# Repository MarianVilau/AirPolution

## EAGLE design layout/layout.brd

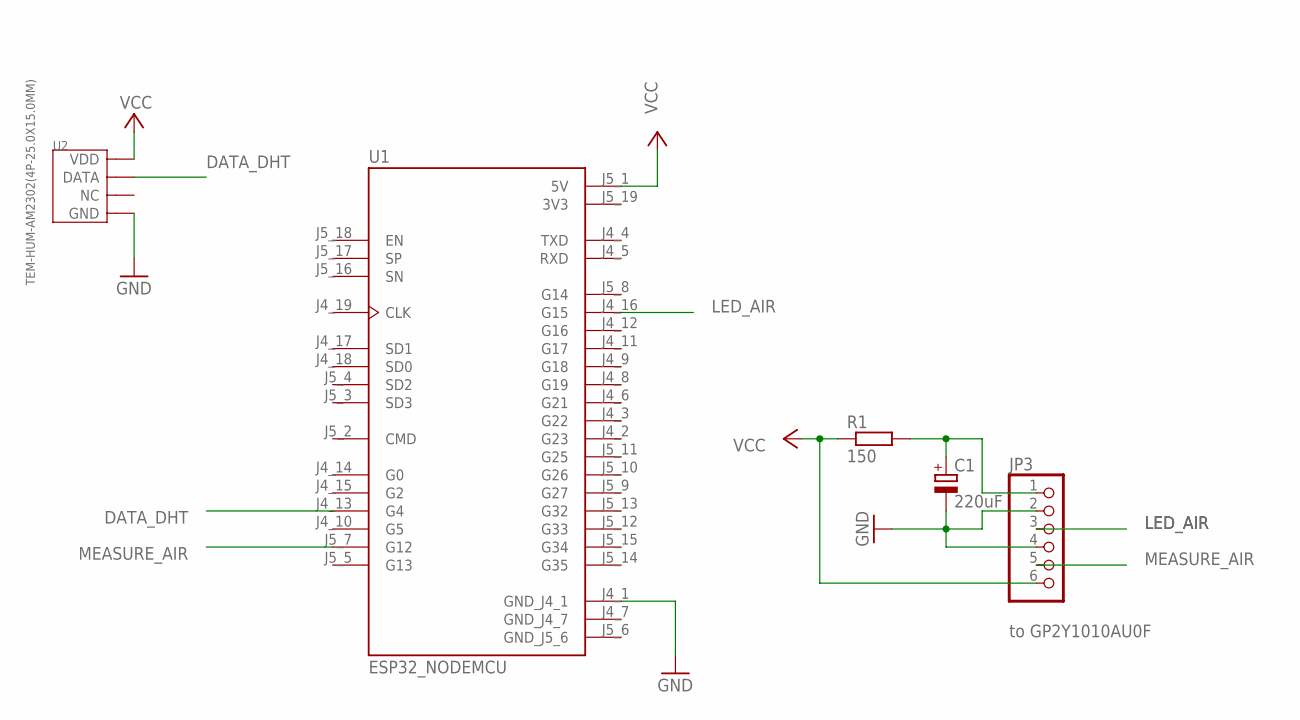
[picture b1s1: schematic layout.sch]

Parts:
C1: 220uF; E2-5
JP3: to GP2Y1010AU0F; 1X06
R1: 150; 0204/7
U1: ESP32_NODEMCU; MODULE_ESP32_NODEMCU
U2: TEM-HUM-AM2302(4P-25.0X15.0MM); SNR4-2.54-25.0X15.0X7.0MM

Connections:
3V3: U1.J5_19 (3V3)
DATA_DHT: U1.J4_13 (G4), U2.P$2 (DATA)
GND: C1.-, JP3.2, JP3.4, U1.J4_1 (GND_J4_1), U2.P$4 (GND)
GND_J4_7: U1.J4_7 (GND_J4_7)
GND_J5_6: U1.J5_6 (GND_J5_6)
LED_AIR: JP3.3, U1.J4_16 (G15)
MEASURE_AIR: JP3.5, U1.J5_7 (G12)
unnamed: C1.+, JP3.1, R1.2
VCC: JP3.6, R1.1, U1.J5_1 (5V), U2.P$1 (VDD)

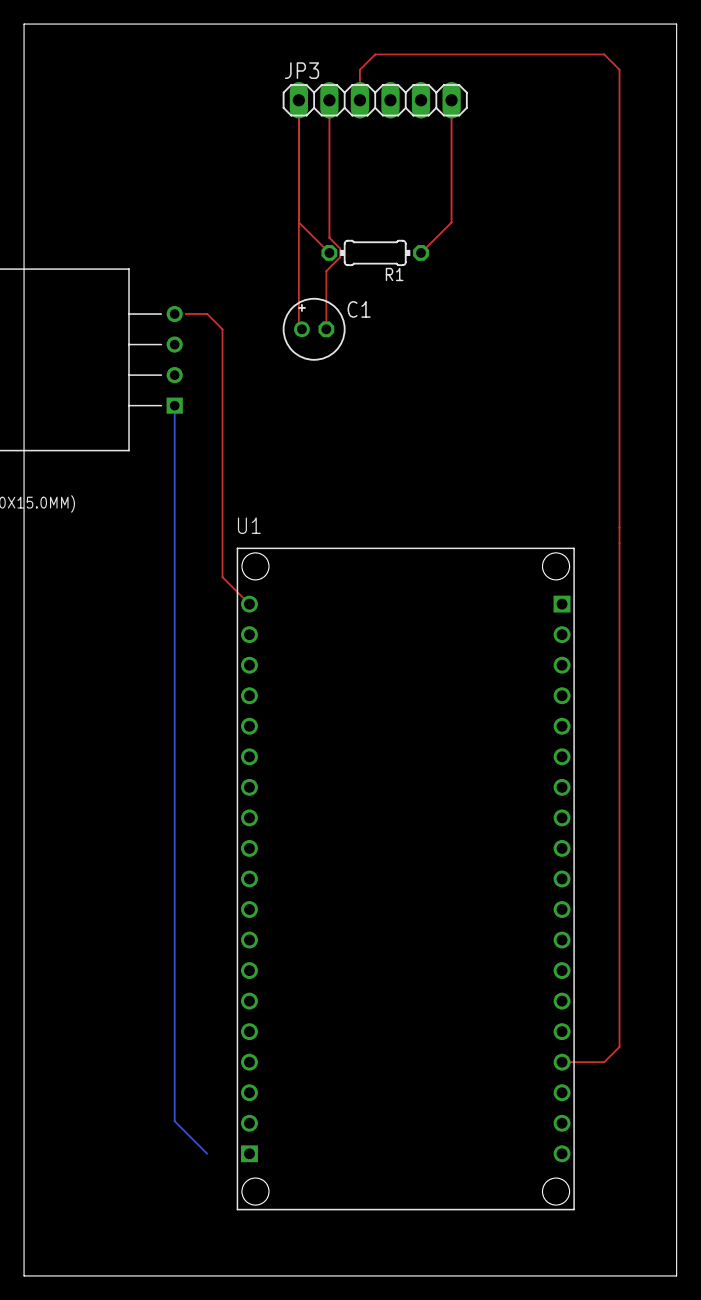
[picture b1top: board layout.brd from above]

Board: 2 copper layers, 54.3 x 104.1 mm, 5 parts (0 on the bottom side), 6 nets.

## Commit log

2023-11-17 functional dust sensor
2023-11-17 functional temperature&humidity sensor
2023-11-17 wifi connection and json creator
2023-11-17 Sensors receiver server
2023-11-17 clock functional
2023-11-17 add gitignore
2023-11-17 add data sender and session var
2023-11-17 good connexion with server
2023-11-17 MongoDB integration
2023-11-18 Code refactoring
2023-11-18 last before dead
